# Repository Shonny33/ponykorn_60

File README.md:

# ponykorn 60
 O-ring mount 60% pcb. This PCB was design and replicated from the orignial Bakeneko60 which taught me how to design my own PCB. So thank you Katano! And thank you
 again for helping me with all the questions I had when designing this back then before the release of the bakeneko60 Sept-Oct, 2020.
 
 # Q&A.
  ## Is it usable?
  To be honest I do not know haha, I have yet to have one printed and tested for over a year (do to chip shortages) now but hopefully it works.
  ## Would this work with the current bakeneko?
  In theory I would assume so, but again I have yet to try it out for myself to say yes.
  ## Would you ever run GB for this?
  No haha this PCB is only used for educational purposes for myself if you would like to support the original creator 
  (@kkatano) I would highly suggest you do so!

## Layouts

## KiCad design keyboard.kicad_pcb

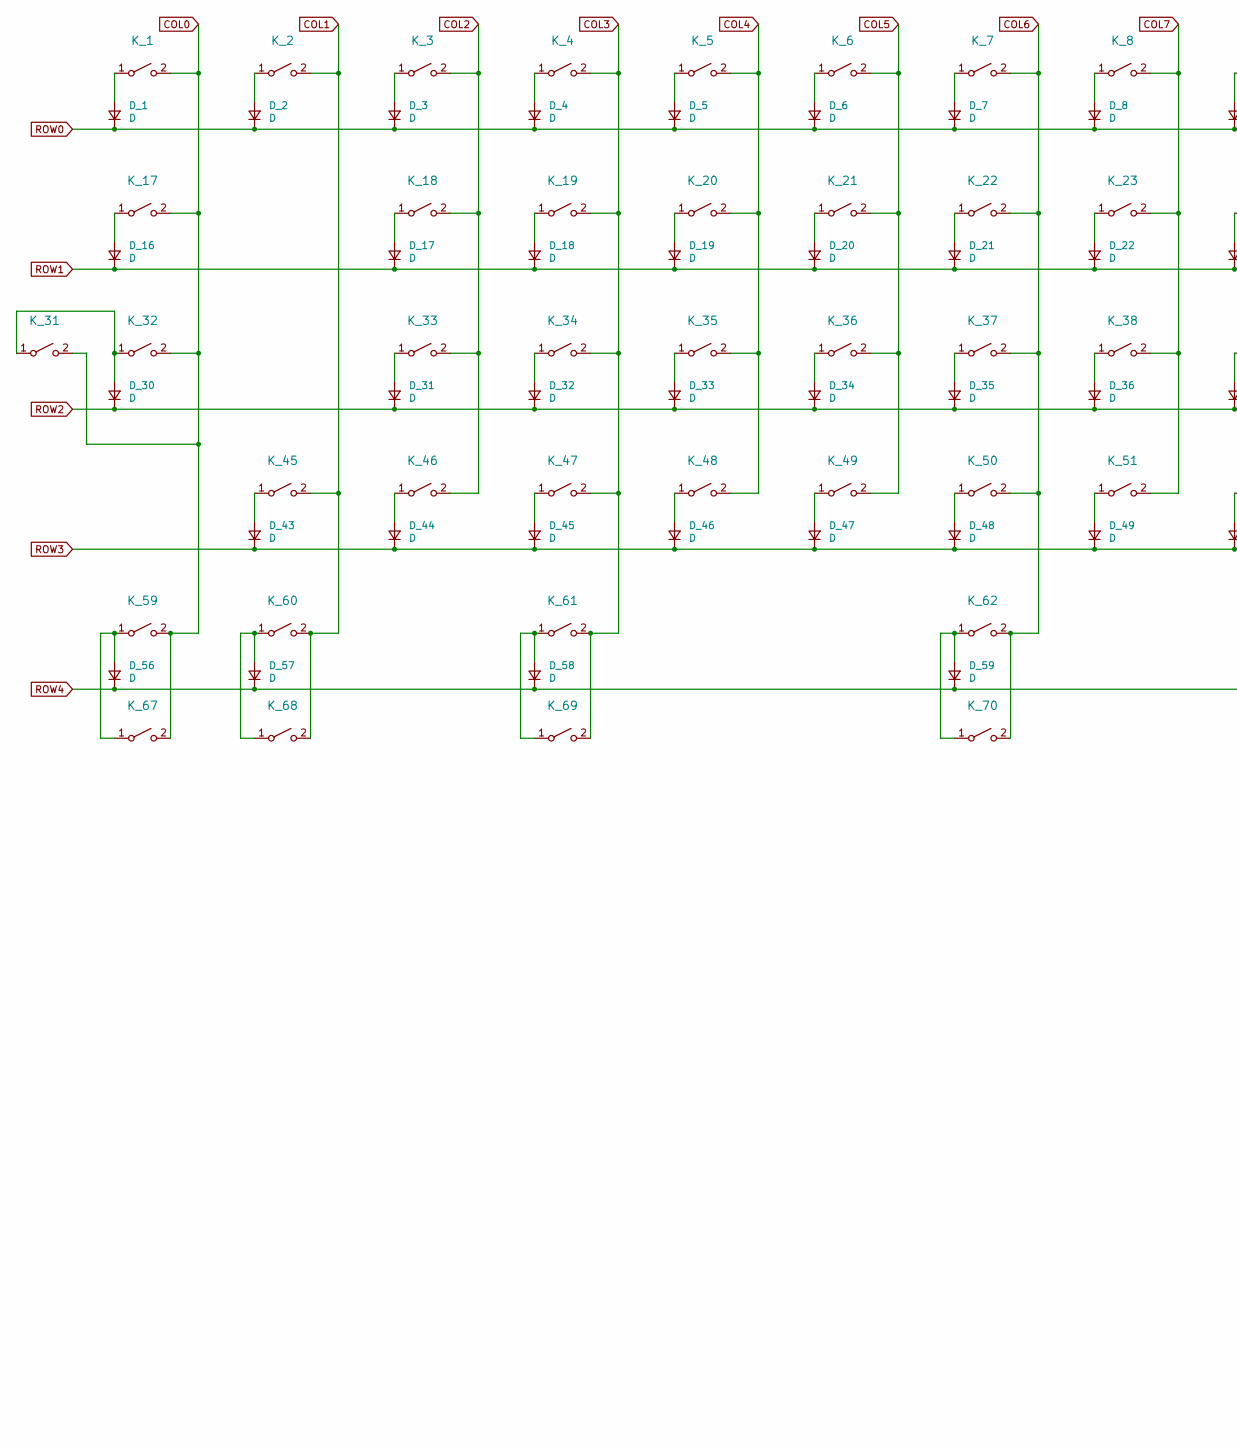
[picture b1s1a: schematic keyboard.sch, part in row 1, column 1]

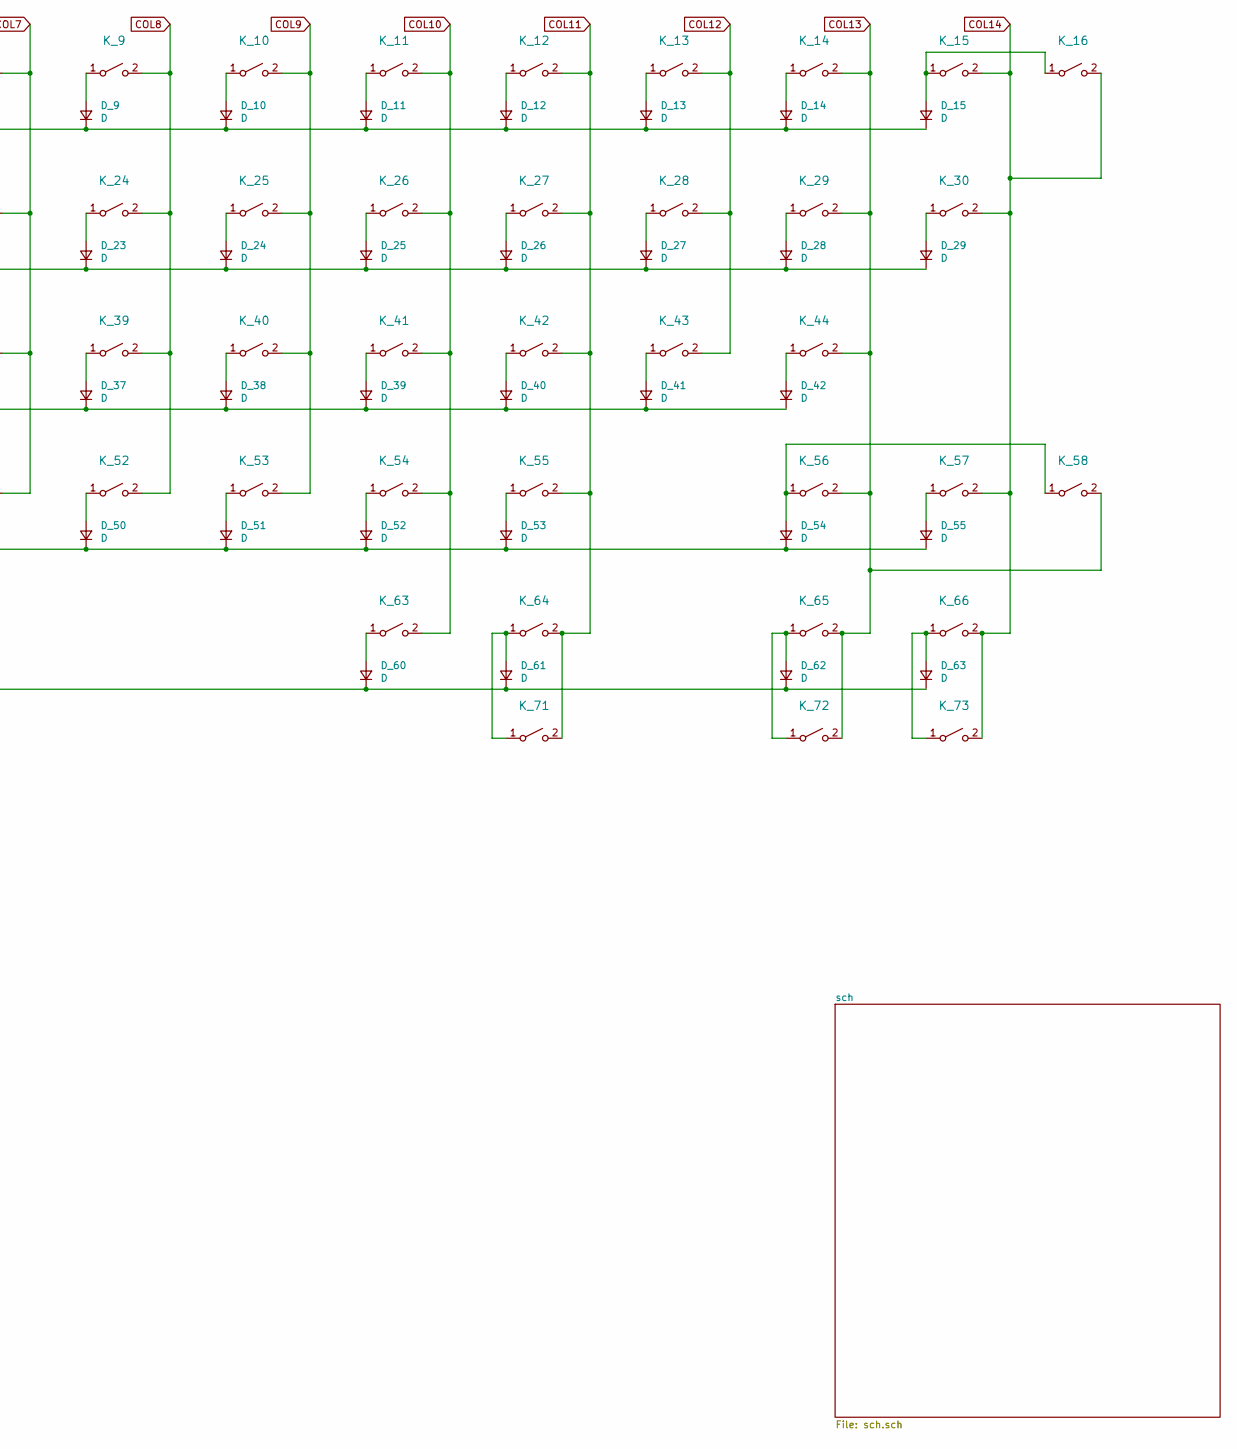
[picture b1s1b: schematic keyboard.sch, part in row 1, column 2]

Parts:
D_1, D_2, D_3, D_4, D_5, D_6, D_7, D_8, D_9, D_10, D_11, D_12, D_13, D_14, D_15, D_16, D_17, D_18, D_19, D_20, D_21, D_22, D_23, D_24, D_25, D_26, D_27, D_28, D_29, D_30, D_31, D_32, D_33, D_34, D_35, D_36, D_37, D_38, D_39, D_40, D_41, D_42, D_43, D_44, D_45, D_46, D_47, D_48, D_49, D_50, D_51, D_52, D_53, D_54, D_55, D_56, D_57, D_58, D_59, D_60, D_61, D_62, D_63: D; D_SOD-123
K_1, K_2, K_3, K_4, K_5, K_6, K_7, K_8, K_9, K_10, K_11, K_12, K_13, K_14, K_16, K_18, K_19, K_20, K_21, K_22, K_23, K_24, K_25, K_26, K_27, K_28, K_29, K_33, K_34, K_35, K_36, K_37, K_38, K_39, K_40, K_41, K_42, K_43, K_46, K_47, K_48, K_49, K_50, K_51, K_52, K_53, K_54, K_55, K_57, K_68, K_72: KEYSW; MXOnly-1U-NoLED
K_15: KEYSW; MXOnly-2U-NoLED
K_17, K_30, K_64, K_66, K_67, K_69: KEYSW; MXOnly-1.5U-NoLED
K_31, K_58: KEYSW; MXOnly-1.75U-NoLED
K_32, K_59, K_60, K_61, K_63, K_65, K_71, K_73: KEYSW; MXOnly-1.25U-NoLED
K_44, K_45: KEYSW; MXOnly-2.25U-NoLED
K_56: KEYSW; MXOnly-2.75U-NoLED
K_62: KEYSW; MXOnly-6.25U-ReversedStabilizers-NoLED
K_70: KEYSW; MXOnly-7U-ReversedStabilizers-NoLED

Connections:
COL0: K_1.2 (B), K_17.2 (B), K_31.2 (B), K_32.2 (B), K_59.2 (B), K_67.2 (B); also elsewhere on the board
COL1: K_2.2 (B), K_45.2 (B), K_60.2 (B), K_68.2 (B); also elsewhere on the board
COL2: K_3.2 (B), K_18.2 (B), K_33.2 (B), K_46.2 (B); also elsewhere on the board
COL3: K_4.2 (B), K_19.2 (B), K_34.2 (B), K_47.2 (B), K_61.2 (B), K_69.2 (B); also elsewhere on the board
COL4: K_5.2 (B), K_20.2 (B), K_35.2 (B), K_48.2 (B); also elsewhere on the board
COL5: K_6.2 (B), K_21.2 (B), K_36.2 (B), K_49.2 (B); also elsewhere on the board
COL6: K_7.2 (B), K_22.2 (B), K_37.2 (B), K_50.2 (B), K_62.2 (B), K_70.2 (B); also elsewhere on the board
COL7: K_8.2 (B), K_23.2 (B), K_38.2 (B), K_51.2 (B); also elsewhere on the board
COL8: K_9.2 (B), K_24.2 (B), K_39.2 (B), K_52.2 (B); also elsewhere on the board
COL9: K_10.2 (B), K_25.2 (B), K_40.2 (B), K_53.2 (B); also elsewhere on the board
COL10: K_11.2 (B), K_26.2 (B), K_41.2 (B), K_54.2 (B), K_63.2 (B); also elsewhere on the board
COL11: K_12.2 (B), K_27.2 (B), K_42.2 (B), K_55.2 (B), K_64.2 (B), K_71.2 (B); also elsewhere on the board
COL12: K_13.2 (B), K_28.2 (B), K_43.2 (B); also elsewhere on the board
COL13: K_14.2 (B), K_29.2 (B), K_44.2 (B), K_56.2 (B), K_58.2 (B), K_65.2 (B), K_72.2 (B); also elsewhere on the board
COL14: K_15.2 (B), K_16.2 (B), K_30.2 (B), K_57.2 (B), K_66.2 (B), K_73.2 (B); also elsewhere on the board
unnamed: D_1.2 (A), K_1.1 (A)
unnamed: D_2.2 (A), K_2.1 (A)
unnamed: D_3.2 (A), K_3.1 (A)
unnamed: D_4.2 (A), K_4.1 (A)
unnamed: D_5.2 (A), K_5.1 (A)
unnamed: D_6.2 (A), K_6.1 (A)
unnamed: D_7.2 (A), K_7.1 (A)
unnamed: D_8.2 (A), K_8.1 (A)
unnamed: D_9.2 (A), K_9.1 (A)
unnamed: D_10.2 (A), K_10.1 (A)
unnamed: D_11.2 (A), K_11.1 (A)
unnamed: D_12.2 (A), K_12.1 (A)
unnamed: D_13.2 (A), K_13.1 (A)
unnamed: D_14.2 (A), K_14.1 (A)
unnamed: D_15.2 (A), K_15.1 (A), K_16.1 (A)
unnamed: D_16.2 (A), K_17.1 (A)
unnamed: D_17.2 (A), K_18.1 (A)
unnamed: D_18.2 (A), K_19.1 (A)
unnamed: D_19.2 (A), K_20.1 (A)
unnamed: D_20.2 (A), K_21.1 (A)
unnamed: D_21.2 (A), K_22.1 (A)
unnamed: D_22.2 (A), K_23.1 (A)
unnamed: D_23.2 (A), K_24.1 (A)
unnamed: D_24.2 (A), K_25.1 (A)
unnamed: D_25.2 (A), K_26.1 (A)
unnamed: D_26.2 (A), K_27.1 (A)
unnamed: D_27.2 (A), K_28.1 (A)
unnamed: D_28.2 (A), K_29.1 (A)
unnamed: D_29.2 (A), K_30.1 (A)
unnamed: D_30.2 (A), K_31.1 (A), K_32.1 (A)
unnamed: D_31.2 (A), K_33.1 (A)
unnamed: D_32.2 (A), K_34.1 (A)
unnamed: D_33.2 (A), K_35.1 (A)
unnamed: D_34.2 (A), K_36.1 (A)
unnamed: D_35.2 (A), K_37.1 (A)
unnamed: D_36.2 (A), K_38.1 (A)
unnamed: D_37.2 (A), K_39.1 (A)
unnamed: D_38.2 (A), K_40.1 (A)
unnamed: D_39.2 (A), K_41.1 (A)
unnamed: D_40.2 (A), K_42.1 (A)
unnamed: D_41.2 (A), K_43.1 (A)
unnamed: D_42.2 (A), K_44.1 (A)
unnamed: D_43.2 (A), K_45.1 (A)
unnamed: D_44.2 (A), K_46.1 (A)
unnamed: D_45.2 (A), K_47.1 (A)
unnamed: D_46.2 (A), K_48.1 (A)
unnamed: D_47.2 (A), K_49.1 (A)
unnamed: D_48.2 (A), K_50.1 (A)
unnamed: D_49.2 (A), K_51.1 (A)
unnamed: D_50.2 (A), K_52.1 (A)
unnamed: D_51.2 (A), K_53.1 (A)
unnamed: D_52.2 (A), K_54.1 (A)
unnamed: D_53.2 (A), K_55.1 (A)
unnamed: D_54.2 (A), K_56.1 (A), K_58.1 (A)
unnamed: D_55.2 (A), K_57.1 (A)
unnamed: D_56.2 (A), K_59.1 (A), K_67.1 (A)
unnamed: D_57.2 (A), K_60.1 (A), K_68.1 (A)
unnamed: D_58.2 (A), K_61.1 (A), K_69.1 (A)
unnamed: D_59.2 (A), K_62.1 (A), K_70.1 (A)
unnamed: D_60.2 (A), K_63.1 (A)
unnamed: D_61.2 (A), K_64.1 (A), K_71.1 (A)
unnamed: D_62.2 (A), K_65.1 (A), K_72.1 (A)
unnamed: D_63.2 (A), K_66.1 (A), K_73.1 (A)
ROW0: D_1.1 (K), D_2.1 (K), D_3.1 (K), D_4.1 (K), D_5.1 (K), D_6.1 (K), D_7.1 (K), D_8.1 (K), D_9.1 (K), D_10.1 (K), D_11.1 (K), D_12.1 (K), D_13.1 (K), D_14.1 (K), D_15.1 (K); also elsewhere on the board
ROW1: D_16.1 (K), D_17.1 (K), D_18.1 (K), D_19.1 (K), D_20.1 (K), D_21.1 (K), D_22.1 (K), D_23.1 (K), D_24.1 (K), D_25.1 (K), D_26.1 (K), D_27.1 (K), D_28.1 (K), D_29.1 (K); also elsewhere on the board
ROW2: D_30.1 (K), D_31.1 (K), D_32.1 (K), D_33.1 (K), D_34.1 (K), D_35.1 (K), D_36.1 (K), D_37.1 (K), D_38.1 (K), D_39.1 (K), D_40.1 (K), D_41.1 (K), D_42.1 (K); also elsewhere on the board
ROW3: D_43.1 (K), D_44.1 (K), D_45.1 (K), D_46.1 (K), D_47.1 (K), D_48.1 (K), D_49.1 (K), D_50.1 (K), D_51.1 (K), D_52.1 (K), D_53.1 (K), D_54.1 (K), D_55.1 (K); also elsewhere on the board
ROW4: D_56.1 (K), D_57.1 (K), D_58.1 (K), D_59.1 (K), D_60.1 (K), D_61.1 (K), D_62.1 (K), D_63.1 (K); also elsewhere on the board

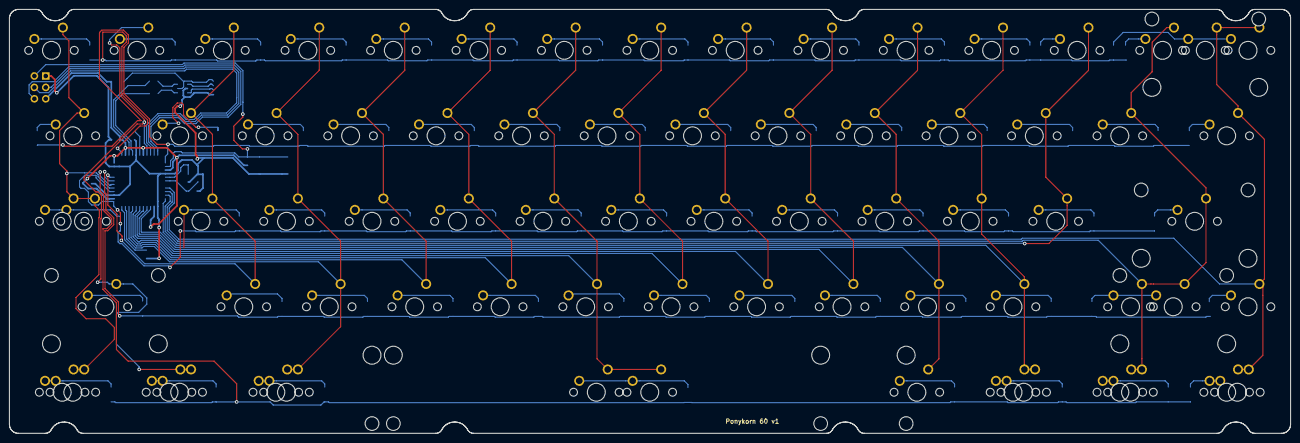
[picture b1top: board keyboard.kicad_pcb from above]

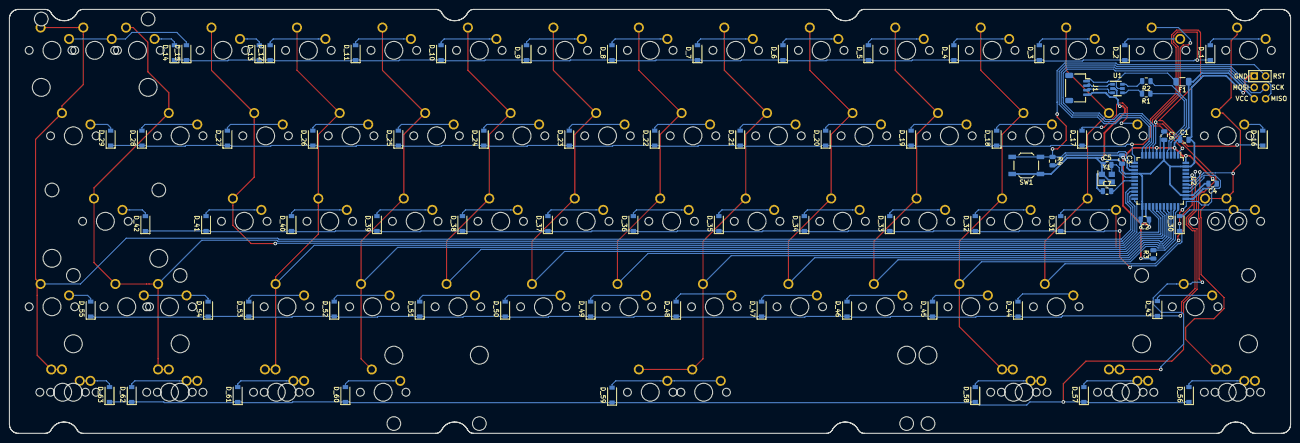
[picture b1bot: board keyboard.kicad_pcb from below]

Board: 2 copper layers, 285.6 x 94.5 mm, 154 parts (81 on the bottom side), 100 nets.

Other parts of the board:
C1, C2, C3: 0.1u; C_0805_2012Metric
C4: 10u; C_0805_2012Metric
C5, C7: 22p; C_0805_2012Metric
C6: 1u; C_0805_2012Metric
F1: 500mA; Fuse_1206_3216Metric
J1: JST SH 4-pin; JST_SH_SM04B-SRSS-TB_1x04-1MP_P1.00mm_Horizontal
J2: AVR-ISP-6; Reset_Pretty
R1, R2: 22; R_0805_2012Metric
R3, R4: 10k; R_0805_2012Metric
SW1: Reset; SW_SPST_TL3342
U1: USBLC6-2SC6; SOT-23-6
U2: ATmega32U4-AU; TQFP-44_10x10mm_P0.8mm
Y1: 16MHz; Crystal_SMD_3225-4Pin_3.2x2.5mm

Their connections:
+5V: C1.1, C2.1, C3.1, C4.1, F1.1, J2.2, R4.2, U2.2, U2.7, U2.14, U2.24, U2.34, U2.44
/sch/MCU_D+: R1.1, U2.4
/sch/MCU_D-: R2.1, U2.3
COL0: U2.37; also elsewhere on the board
COL1: U2.8; also elsewhere on the board
COL2: U2.40; also elsewhere on the board
COL3: U2.32; also elsewhere on the board
COL4: U2.31; also elsewhere on the board
COL5: U2.30; also elsewhere on the board
COL6: U2.29; also elsewhere on the board
COL7: U2.28; also elsewhere on the board
COL8: U2.27; also elsewhere on the board
COL9: U2.26; also elsewhere on the board
COL10: U2.25; also elsewhere on the board
COL11: U2.22; also elsewhere on the board
COL12: U2.21; also elsewhere on the board
COL13: U2.20; also elsewhere on the board
COL14: U2.19; also elsewhere on the board
D+: J1.3, U1.3
D-: J1.2, U1.1
ESD_D+: R1.2, U1.4
ESD_D-: R2.2, U1.6
GND: C1.2, C2.2, C3.2, C4.2, C5.1, C6.2, C7.1, J1.4, J2.6, R3.1, SW1.1, U1.2, U2.5, U2.15, U2.23, U2.35, U2.43, Y1.2, Y1.4
MISO: J2.1, U2.11
MOSI: J2.4, U2.10
unnamed: C6.1, U2.6
unnamed: R3.2, U2.33
RESET: J2.5, R4.1, SW1.2, U2.13
ROW0: U2.1; also elsewhere on the board
ROW1: U2.12; also elsewhere on the board
ROW2: U2.36; also elsewhere on the board
ROW3: U2.39; also elsewhere on the board
ROW4: U2.38; also elsewhere on the board
SCK: J2.3, U2.9
VBUS: F1.2, J1.1, U1.5
XTAL1: C7.2, U2.17, Y1.1
XTAL2: C5.2, U2.16, Y1.3

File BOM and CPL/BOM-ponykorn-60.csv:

Comment,Designator,Footprint,LCSC Part Number
0.1u,"C1,C2,C3",Capacitor_SMD:C_0805_2012Metric,C49678
10u,C4,Capacitor_SMD:C_0805_2012Metric,C15850
22p,"C5,C7",Capacitor_SMD:C_0805_2012Metric,C1804
1u,C6,Capacitor_SMD:C_0805_2012Metric,C28323
D,"D_1,D_2,D_3,D_4,D_5,D_6,D_7,D_8,D_9,D_10,D_11,D_12,D_13,D_14,D_15,D_16,D_17,D_18,D_19,D_20,D_21,D_22,D_23,D_24,D_25,D_26,D_27,D_28,D_29,D_30,D_31,D_32,D_33,D_34,D_35,D_36,D_37,D_38,D_39,D_40,D_41,D_42,D_43,D_44,D_45,D_46,D_47,D_48,D_49,D_50,D_51,D_52,D_53,D_54,D_55,D_56,D_57,D_58,D_59,D_60,D_61,D_62,D_63",Diode_SMD:D_SOD-123,C81598
500mA,F1,Fuse:Fuse_1206_3216Metric,C70076
JST SH 4-pin,J1,Connector_JST:JST_SH_SM04B-SRSS-TB_1x04-1MP_P1.00mm_Horizontal,C160404
AVR-ISP-6,J2,random-keyboard-parts:Reset_Pretty,
KEYSW,"K_1,K_2,K_3,K_4,K_5,K_6,K_7,K_8,K_9,K_10,K_11,K_12,K_13,K_14,K_16,K_18,K_19,K_20,K_21,K_22,K_23,K_24,K_25,K_26,K_27,K_28,K_29,K_33,K_34,K_35,K_36,K_37,K_38,K_39,K_40,K_41,K_42,K_43,K_46,K_47,K_48,K_49,K_50,K_51,K_52,K_53,K_54,K_55,K_57,K_68,K_72",MX_Only:MXOnly-1U-NoLED,
KEYSW,K_15,MX_Only:MXOnly-2U-NoLED,
KEYSW,"K_17,K_30,K_64,K_66,K_67,K_69",MX_Only:MXOnly-1.5U-NoLED,
KEYSW,"K_32,K_59,K_60,K_61,K_63,K_65,K_71,K_73",MX_Only:MXOnly-1.25U-NoLED,
KEYSW,"K_44,K_45",MX_Only:MXOnly-2.25U-NoLED,
KEYSW,K_56,MX_Only:MXOnly-2.75U-NoLED,
KEYSW,"K_31,K_58",MX_Only:MXOnly-1.75U-NoLED,
KEYSW,K_62,MX_Only:MXOnly-6.25U-ReversedStabilizers-NoLED,
KEYSW,K_70,MX_Only:MXOnly-7U-ReversedStabilizers-NoLED,
22,"R1,R2",Resistor_SMD:R_0805_2012Metric,C17561
10k,"R3,R4",Resistor_SMD:R_0805_2012Metric,C17414
Reset,SW1,Button_Switch_SMD:SW_SPST_TL3342,C318884
USBLC6-2SC6,U1,Package_TO_SOT_SMD:SOT-23-6,C7519
ATmega32U4-AU,U2,Package_QFP:TQFP-44_10x10mm_P0.8mm,C44854
16MHz,Y1,Crystal:Crystal_SMD_3225-4Pin_3.2x2.5mm,C13738
